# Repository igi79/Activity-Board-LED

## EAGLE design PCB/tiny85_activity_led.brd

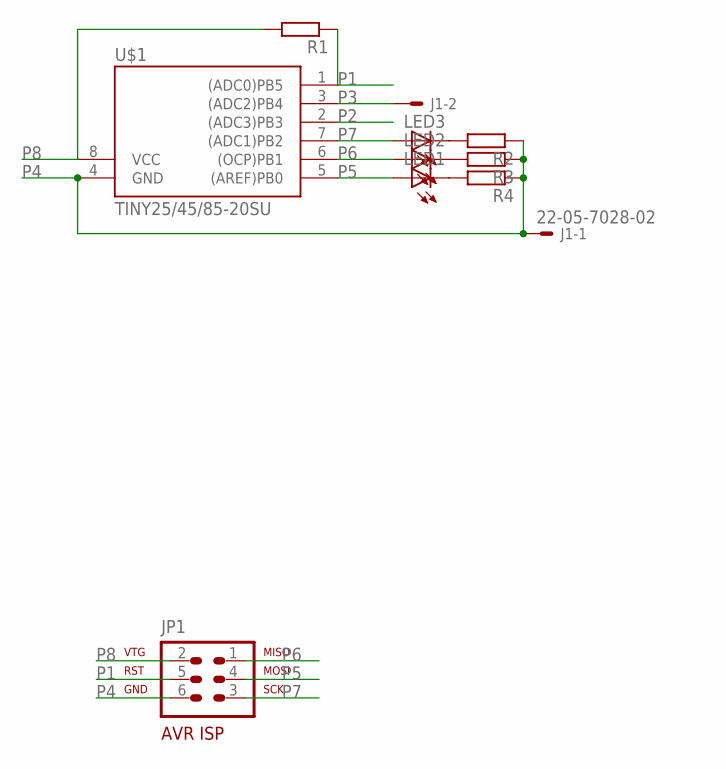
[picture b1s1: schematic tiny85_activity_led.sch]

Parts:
J1: 22-05-7028-02; 7395-02
JP1: AVR-ISP-6R
LED1, LED2, LED3: LED10MM
R1, R2, R3, R4: R-EU_R0805; R0805
U$1: TINY25/45/85-20SU; SOIC8

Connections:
unnamed: LED3.K (C), R2.2
unnamed: LED2.K (C), R3.2
unnamed: LED1.K (C), R4.2
P1: JP1.5, R1.1, U$1.1 ((ADC0)PB5)
P2: U$1.2 ((ADC3)PB3)
P3: J1.2, U$1.3 ((ADC2)PB4)
P4: J1.1, JP1.6, R2.1, R3.1, R4.1, U$1.4 (GND)
P5: JP1.4, LED1.A, U$1.5 ((AREF)PB0)
P6: JP1.1, LED2.A, U$1.6 ((OCP)PB1)
P7: JP1.3, LED3.A, U$1.7 ((ADC1)PB2)
P8: JP1.2, R1.2, U$1.8 (VCC)

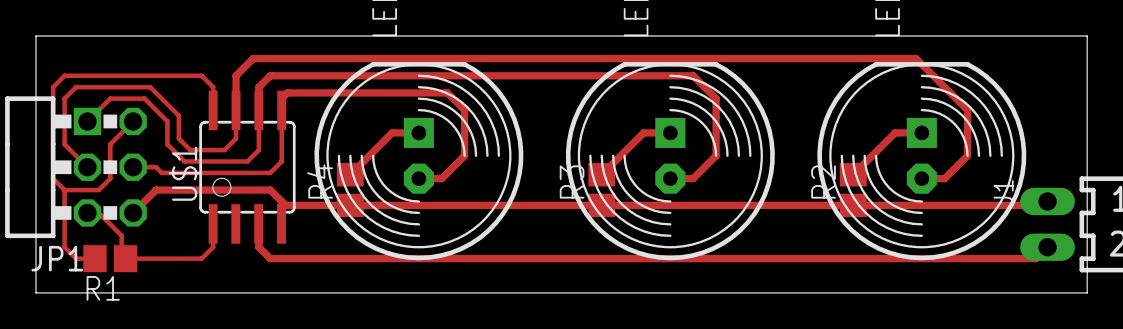
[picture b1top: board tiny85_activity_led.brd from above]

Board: 2 copper layers, 58.4 x 14.3 mm, 10 parts (0 on the bottom side), 10 nets.

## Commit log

2019-01-15 Init
2019-01-15 imgs
